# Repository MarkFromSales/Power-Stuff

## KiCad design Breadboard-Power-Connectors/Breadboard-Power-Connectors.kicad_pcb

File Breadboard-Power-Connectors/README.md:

# Breadboard Power Connectors
I got tired of dealing with mediocre screw terminals on breadboard panels and made this to use banana jacks to link to terminal blocks. There are two pairs spaced to match dual-banana connector cables. One pair has through-hole spaces that either need diodes as designed, a fuse, or simple bridge to connect it through.

## Materials so far

ID | Description | Digi-Key PN
-- | ----------- | -----------
Dx | Schottky Diode Through Hole DO-27, Axial | 80SQ045NRLGOSCT-ND
J2,J4,J6,J8 | TE Connectivity AMP Connectors 01x04 screw terminal block | A98335-ND
J1 | Cal Test Electronics Banana Jack Panel Mount, Through Hole, Right Angle	BLACK  | BKCT3151SP-0-ND
J3 | Cal Test Electronics Banana Jack Panel Mount, Through Hole, Right Angle	RED    | BKCT3151SP-2-ND
J5 | Cal Test Electronics Banana Jack Panel Mount, Through Hole, Right Angle	YELLOW | BKCT3151SP-4-ND
J7 | Cal Test Electronics Banana Jack Panel Mount, Through Hole, Right Angle	GREEN  | BKCT3151SP-5-ND

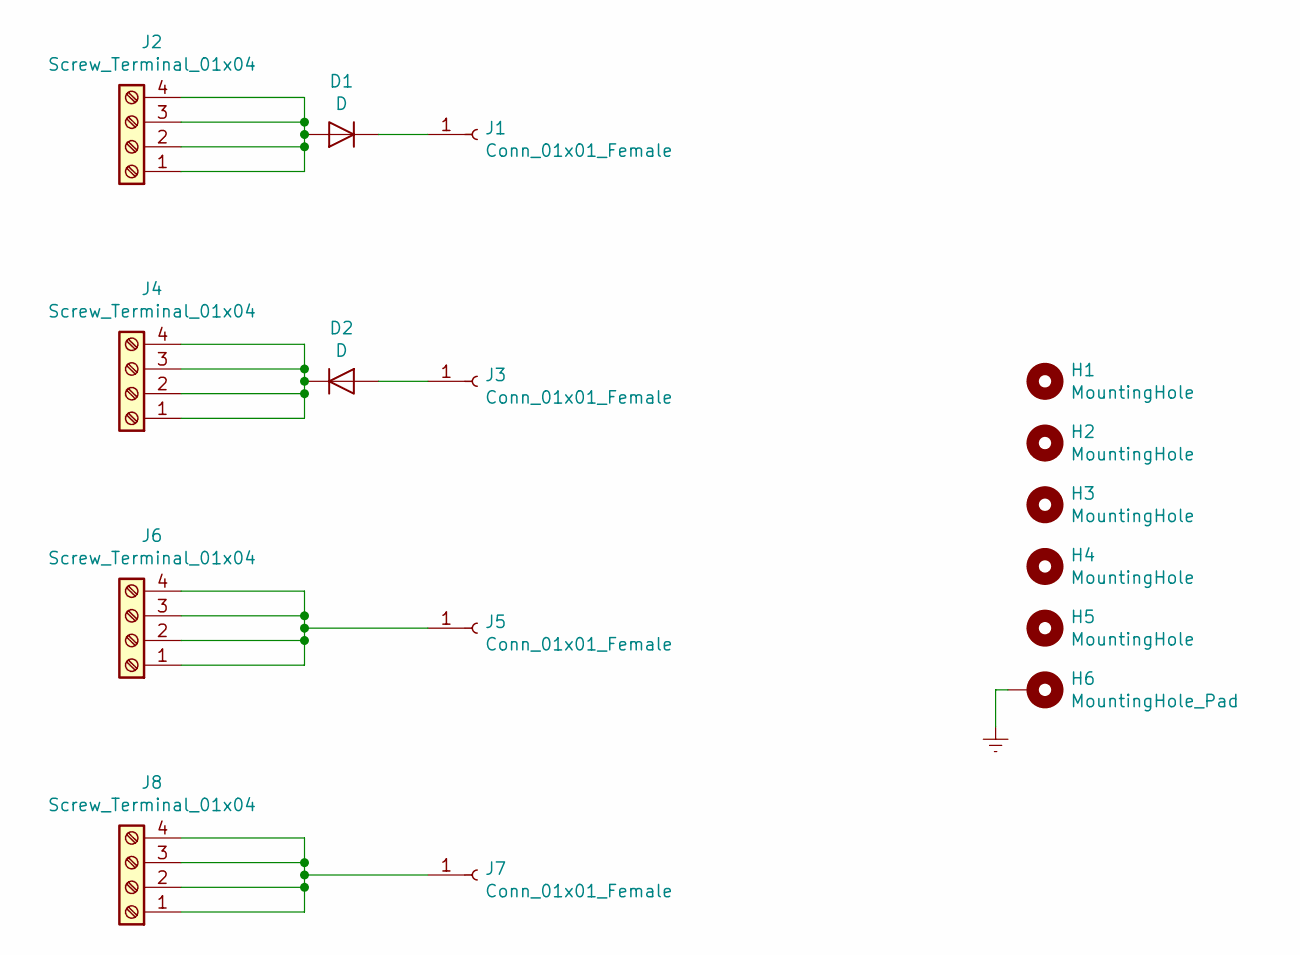
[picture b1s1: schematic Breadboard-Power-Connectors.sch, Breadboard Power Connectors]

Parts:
D1, D2: D; D_DO-27_P12.70mm_Horizontal
H1, H2, H3, H4, H5: MountingHole; MountingHole_3.2mm_M3
H6: MountingHole_Pad; MountingHole_3.2mm_M3_Pad
J1, J3, J5, J7: Conn_01x01_Female; CalTest_CT3151
J2, J4, J6, J8: Screw_Terminal_01x04; TerminalBlock_TE_282834-4_1x04_P2.54mm_Horizontal

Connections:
Earth: H6.1
unnamed: D1.1 (K), J1.1
unnamed: D1.2 (A), J2.1, J2.2, J2.3, J2.4
unnamed: D2.1 (K), J4.1, J4.2, J4.3, J4.4
unnamed: D2.2 (A), J3.1
unnamed: J5.1, J6.1, J6.2, J6.3, J6.4
unnamed: J7.1, J8.1, J8.2, J8.3, J8.4

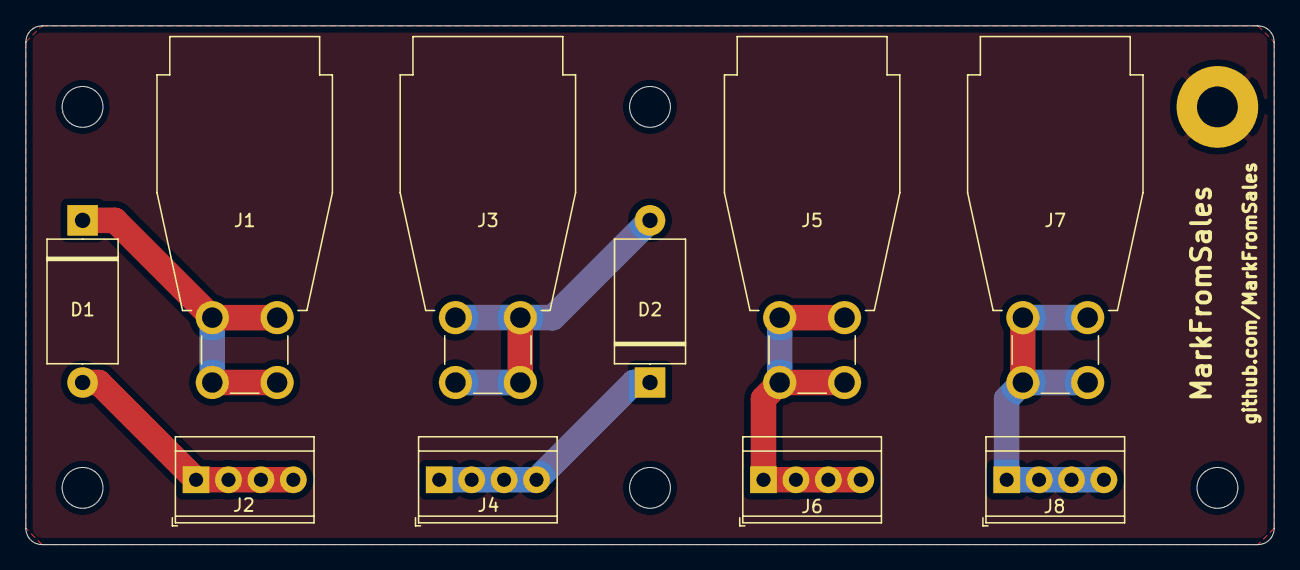
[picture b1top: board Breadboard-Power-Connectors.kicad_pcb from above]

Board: 2 copper layers, 97.8 x 40.6 mm, 16 parts (0 on the bottom side), 6 nets.

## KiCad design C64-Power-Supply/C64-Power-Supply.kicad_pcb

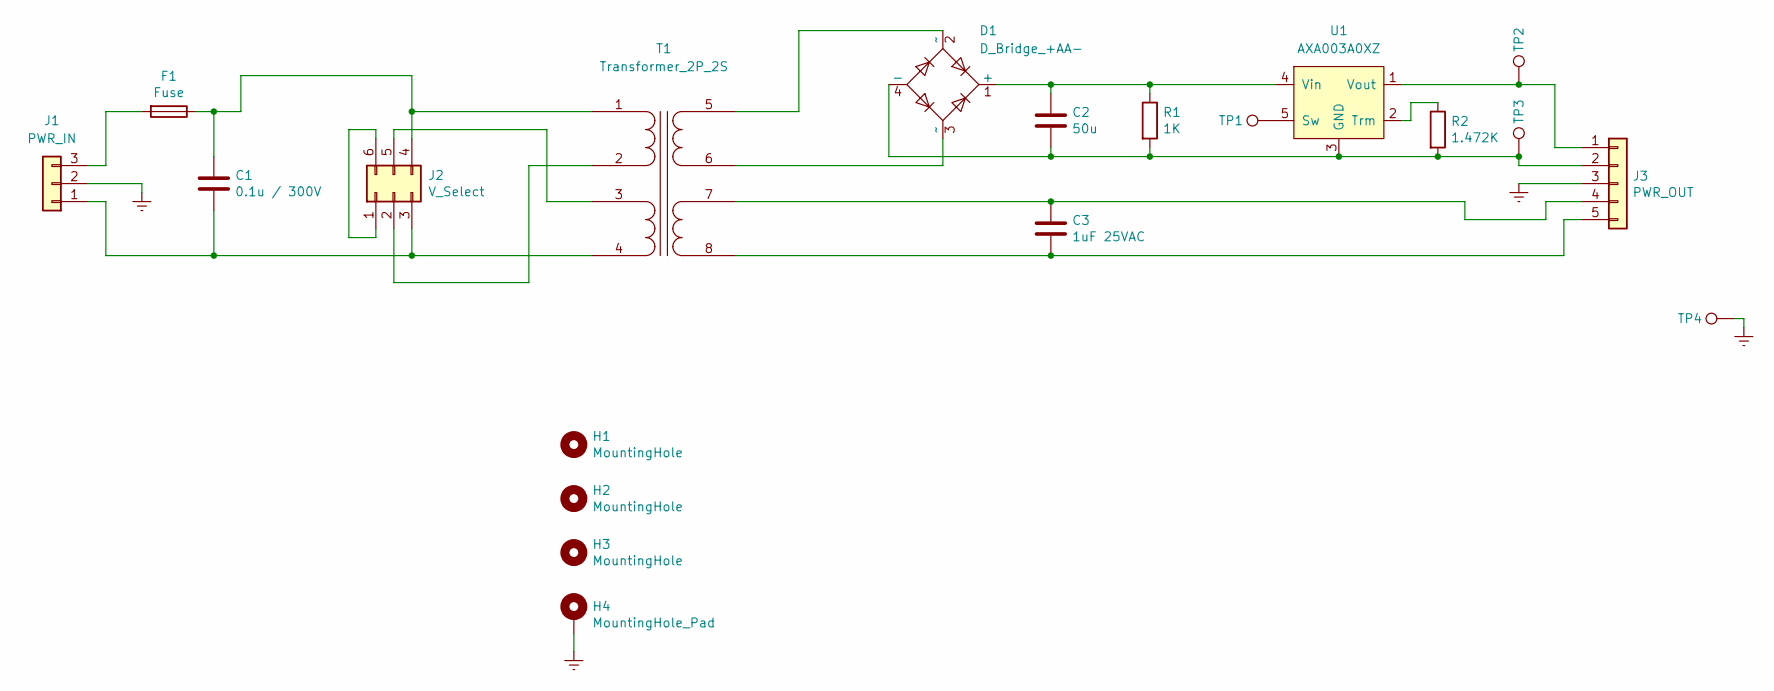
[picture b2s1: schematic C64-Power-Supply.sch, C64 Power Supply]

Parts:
C1: 0.1u / 300V; C_Rect_L26.5mm_W10.5mm_P22.50mm_MKS4
C2: 50u; CP_Axial_L25.0mm_D10.0mm_P30.00mm_Horizontal
C3: 1uF 25VAC; C_Rect_L18.0mm_W11.0mm_P15.00mm_FKS3_FKP3
D1: D_Bridge_+AA-; Diode_Bridge_Vishay_GBU
F1: Fuse; JST_VH_B2P-VH_1x02_P3.96mm_Vertical
H1, H2, H3: MountingHole; MountingHole_3.2mm_M3
H4: MountingHole_Pad; MountingHole_3.2mm_M3_Pad
J1: PWR_IN; JST_VH_B3P-VH_1x03_P3.96mm_Vertical
J2: V_Select; JST_VH_B6P-VH_1x06_P3.96mm_Vertical
J3: PWR_OUT; JST_VH_B5P-VH_1x05_P3.96mm_Vertical
R1: 1K; R_1206_3216Metric_Pad1.42x1.75mm_HandSolder
R2: 1.472K; R_1206_3216Metric_Pad1.42x1.75mm_HandSolder
T1: Transformer_2P_2S; Amgis_L01-6371
TP1, TP2, TP3, TP4: TestPoint; TestPoint_Pad_D2.5mm
U1: AXA003A0XZ

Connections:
Earth: H4.1, J1.2, J3.3, TP4.1
unnamed: C1.1, F1.1, J2.4, T1.1 (IN1A)
unnamed: C1.2, J1.1, J2.3, T1.4 (IN2B)
unnamed: C2.1, D1.1 (+), R1.1, U1.4 (Vin)
unnamed: C2.2, D1.4 (-), J3.2, R1.2, R2.2, TP3.1, U1.3 (GND)
unnamed: C3.1, J3.4, T1.7 (OUT2A)
unnamed: C3.2, J3.5, T1.8 (OUT2B)
unnamed: D1.2 (~~), T1.5 (OUT1A)
unnamed: D1.3 (~~), T1.6 (OUT1B)
unnamed: F1.2, J1.3
unnamed: J2.1, J2.6
unnamed: J2.2, T1.2 (IN1B)
unnamed: J2.5, T1.3 (IN2A)
unnamed: J3.1, TP2.1, U1.1 (Vout)
unnamed: R2.1, U1.2 (Trm)
unnamed: TP1.1, U1.5 (Sw)

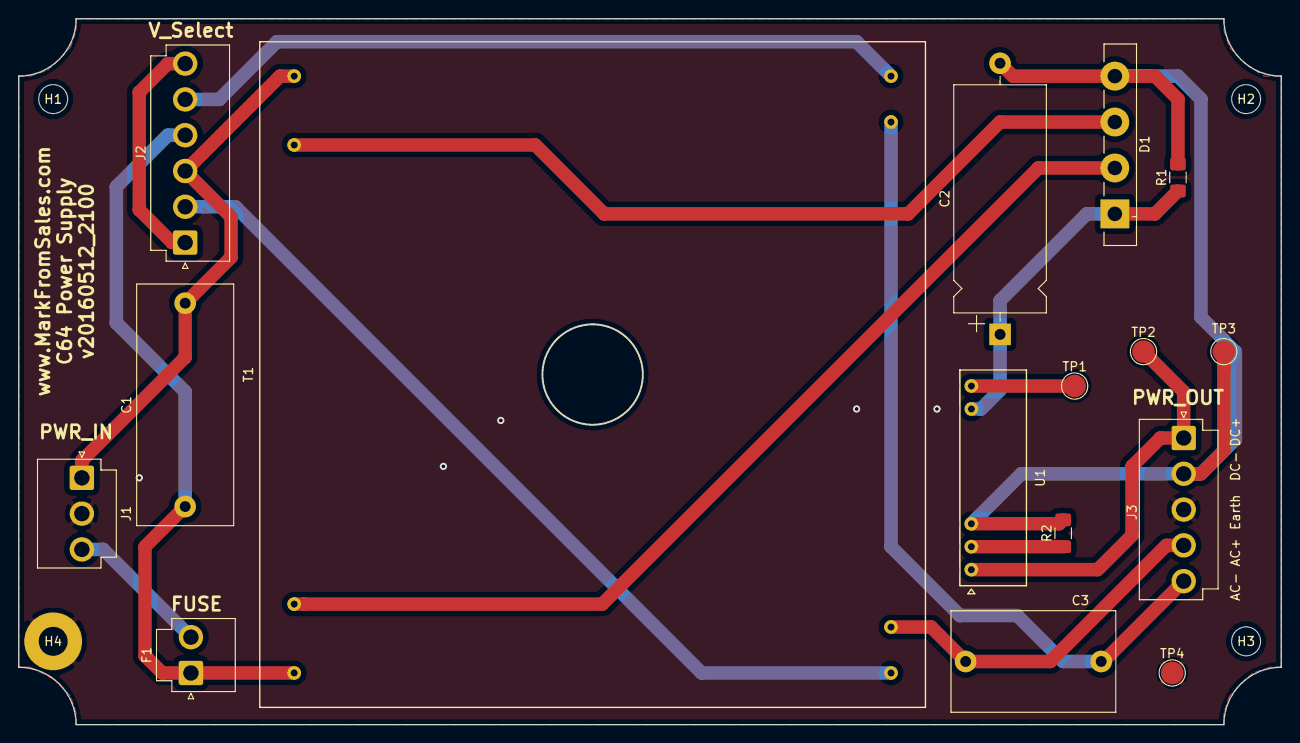
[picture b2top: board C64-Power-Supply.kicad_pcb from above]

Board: 2 copper layers, 139.7 x 78.1 mm, 20 parts (0 on the bottom side), 16 nets.

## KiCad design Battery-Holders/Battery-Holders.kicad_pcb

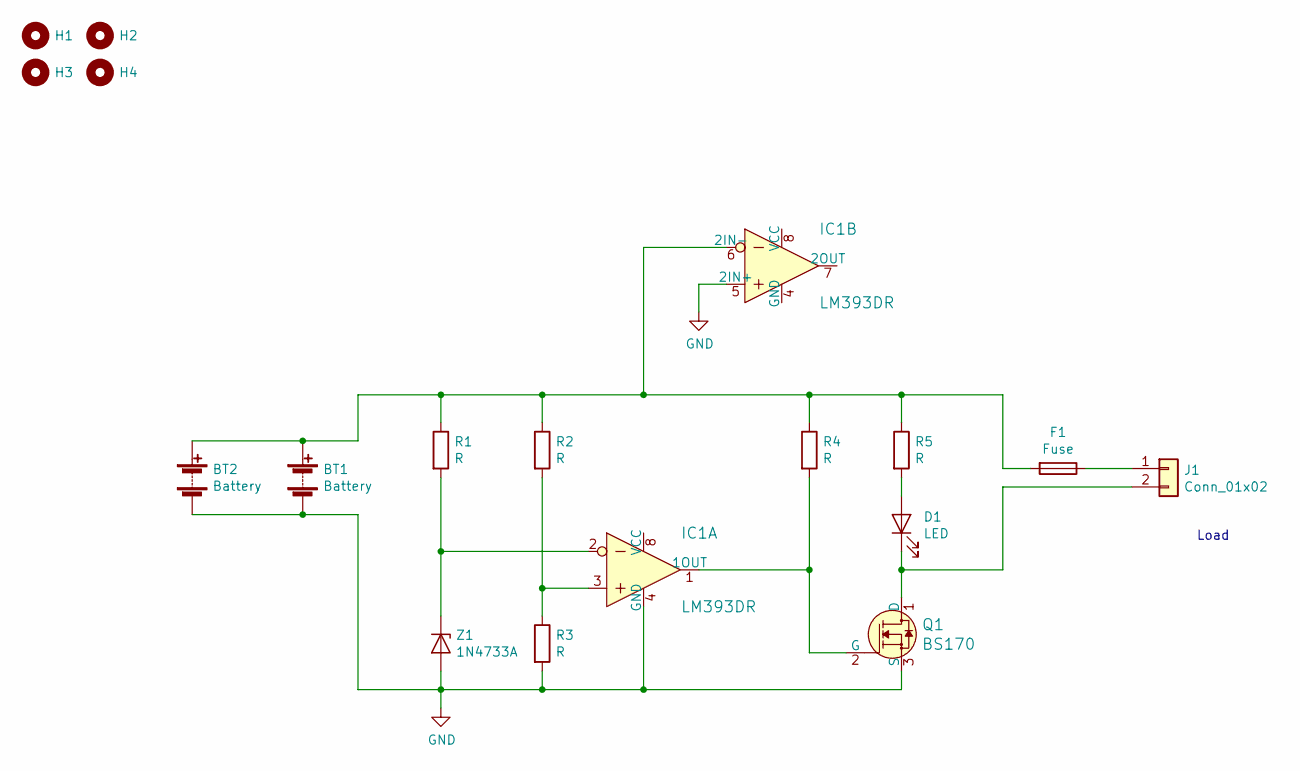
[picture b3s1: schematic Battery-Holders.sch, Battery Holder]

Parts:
BT1, BT2: Battery; BatteryHolder_MPD_BH-18650-PC2
D1: LED; LED_1206_3216Metric_Pad1.42x1.75mm_HandSolder
F1: Fuse; Fuseholder_TR5_Littelfuse_No560_No460
H1, H2, H3, H4: MountingHole; MountingHole_3.2mm_M3
IC1: LM393DR; SOIC-8_3.9x4.9mm_P1.27mm; MPN LM393DR; Digi-Key_PN 296-1015-1-ND
J1: Conn_01x02; JST_VH_B2P-VH_1x02_P3.96mm_Vertical
Q1: BS170; TO-92_Inline_Wide; MPN BS170; Digi-Key_PN BS170-ND
R1, R2, R3, R4, R5: R; R_1206_3216Metric_Pad1.42x1.75mm_HandSolder
Z1: 1N4733A; D_DO-41_SOD81_P10.16mm_Horizontal

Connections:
GND: BT1.2 (-), BT2.2 (-), IC1.4 (GND), IC1.5 (2IN+), Q1.3 (S), R3.2, Z1.2 (A)
unnamed: BT1.1 (+), BT2.1 (+), F1.2, IC1.6 (2IN-), R1.1, R2.1, R4.1, R5.1
unnamed: D1.1 (K), J1.2, Q1.1 (D)
unnamed: D1.2 (A), R5.2
unnamed: F1.1, J1.1
unnamed: IC1.1 (1OUT), Q1.2 (G), R4.2
unnamed: IC1.2, R1.2, Z1.1 (K)
unnamed: IC1.3, R2.2, R3.1

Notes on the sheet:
Load

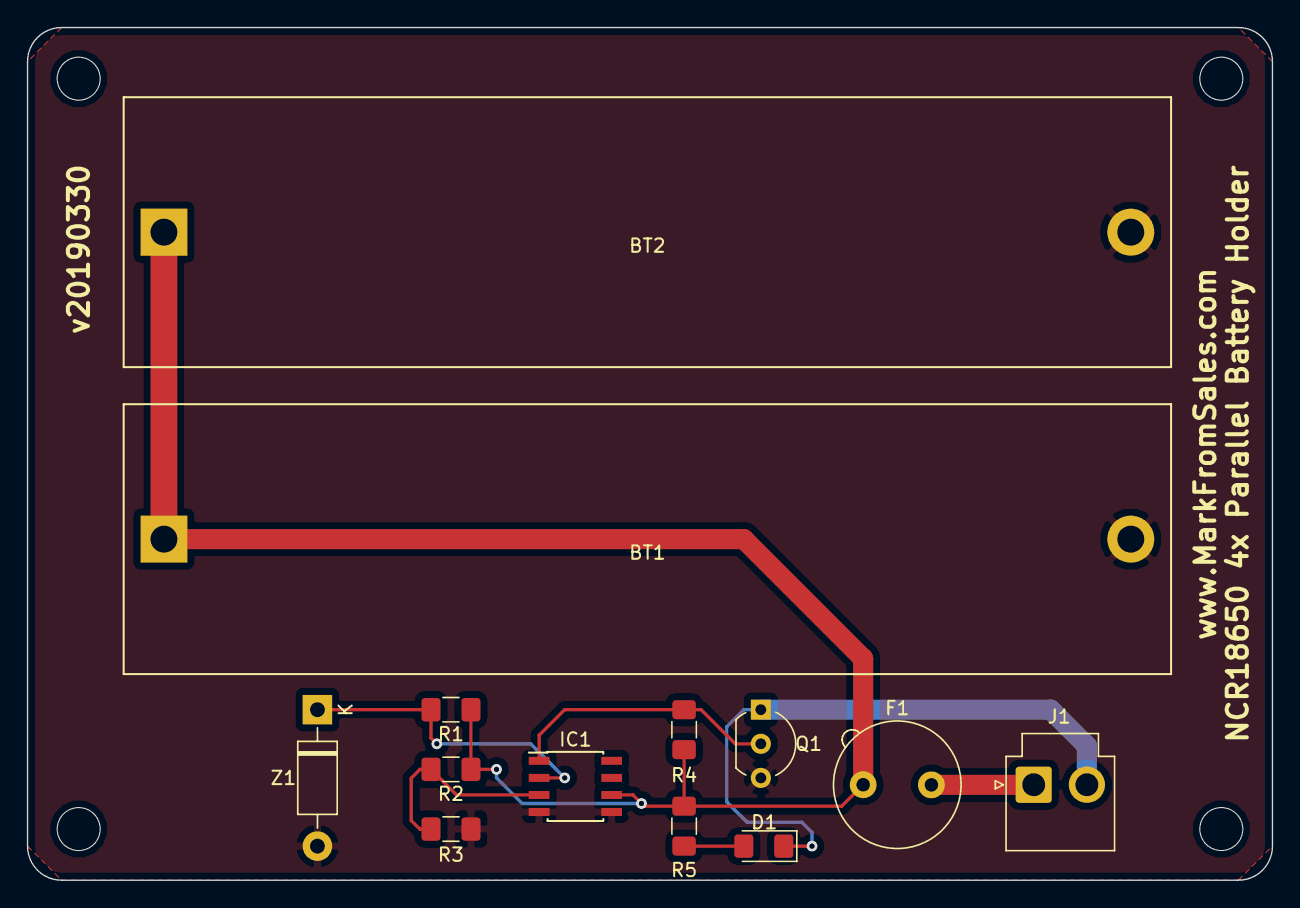
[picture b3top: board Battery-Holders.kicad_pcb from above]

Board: 2 copper layers, 92.7 x 63.5 mm, 17 parts (0 on the bottom side), 8 nets.

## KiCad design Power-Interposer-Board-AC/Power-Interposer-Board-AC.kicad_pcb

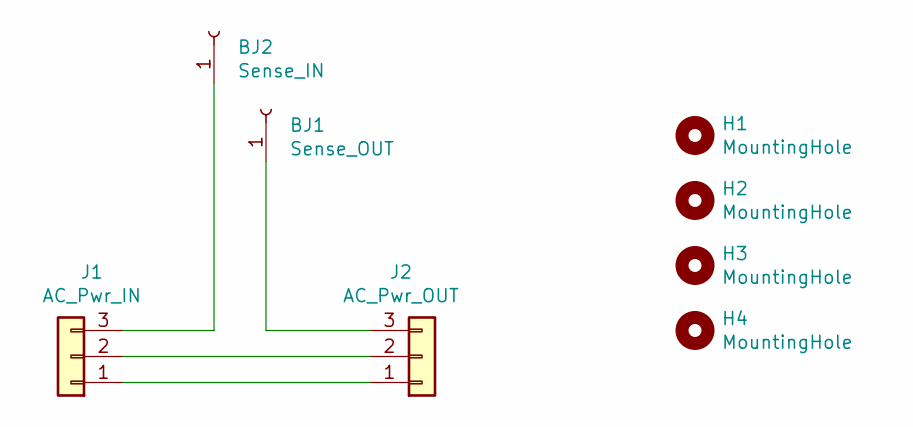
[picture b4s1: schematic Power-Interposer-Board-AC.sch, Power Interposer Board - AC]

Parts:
BJ1: Sense_OUT; CalTest_CT3151
BJ2: Sense_IN; CalTest_CT3151
H1, H2, H3, H4: MountingHole; MountingHole_3.2mm_M3
J1: AC_Pwr_IN; JST_VH_B3PS-VH_1x03_P3.96mm_Horizontal
J2: AC_Pwr_OUT; JST_VH_B3PS-VH_1x03_P3.96mm_Horizontal

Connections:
unnamed: BJ1.1, J2.3
unnamed: BJ2.1, J1.3
unnamed: J1.1, J2.1
unnamed: J1.2, J2.2

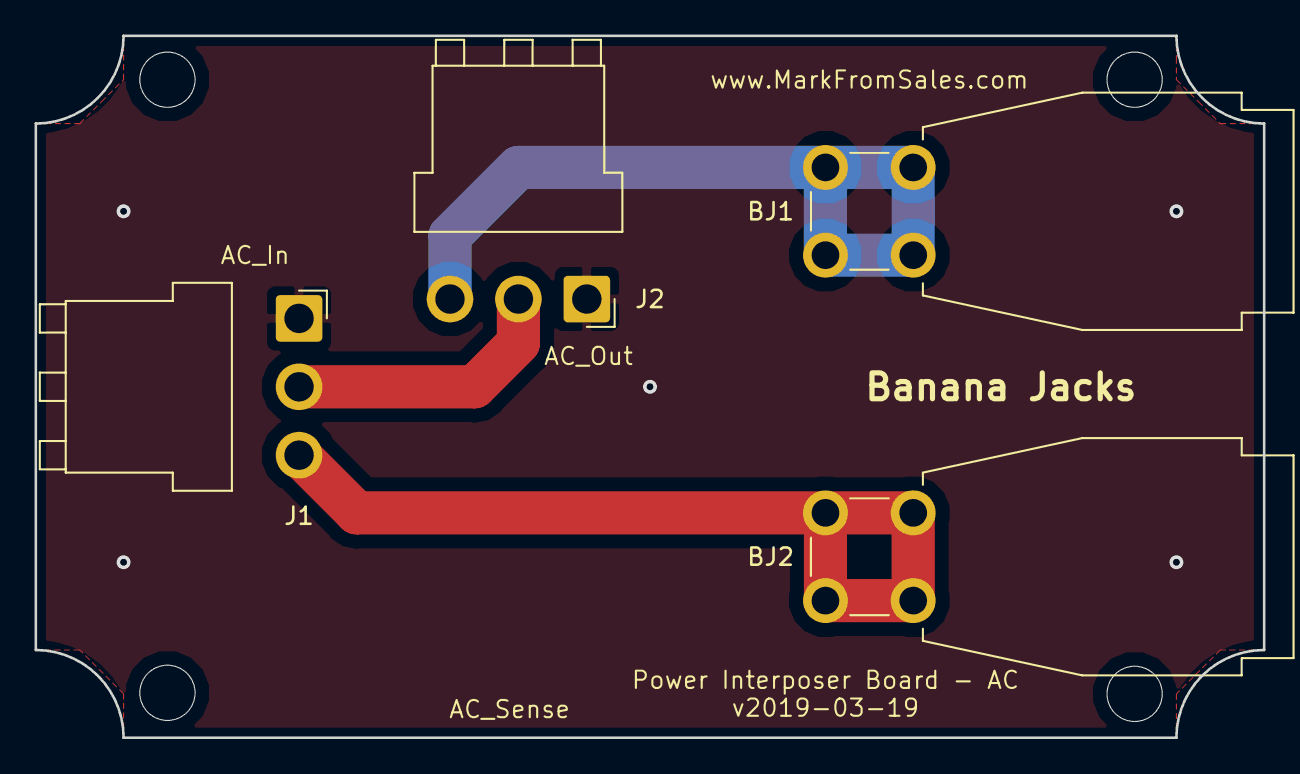
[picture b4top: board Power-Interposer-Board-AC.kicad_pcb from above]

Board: 2 copper layers, 71.1 x 40.6 mm, 8 parts (0 on the bottom side), 4 nets.

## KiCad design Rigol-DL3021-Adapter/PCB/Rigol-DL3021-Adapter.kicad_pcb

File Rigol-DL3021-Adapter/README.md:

# Rigol-DL3021-Adapter
Banana jack adapter for the Rigol DL3021 DC Electronic Load

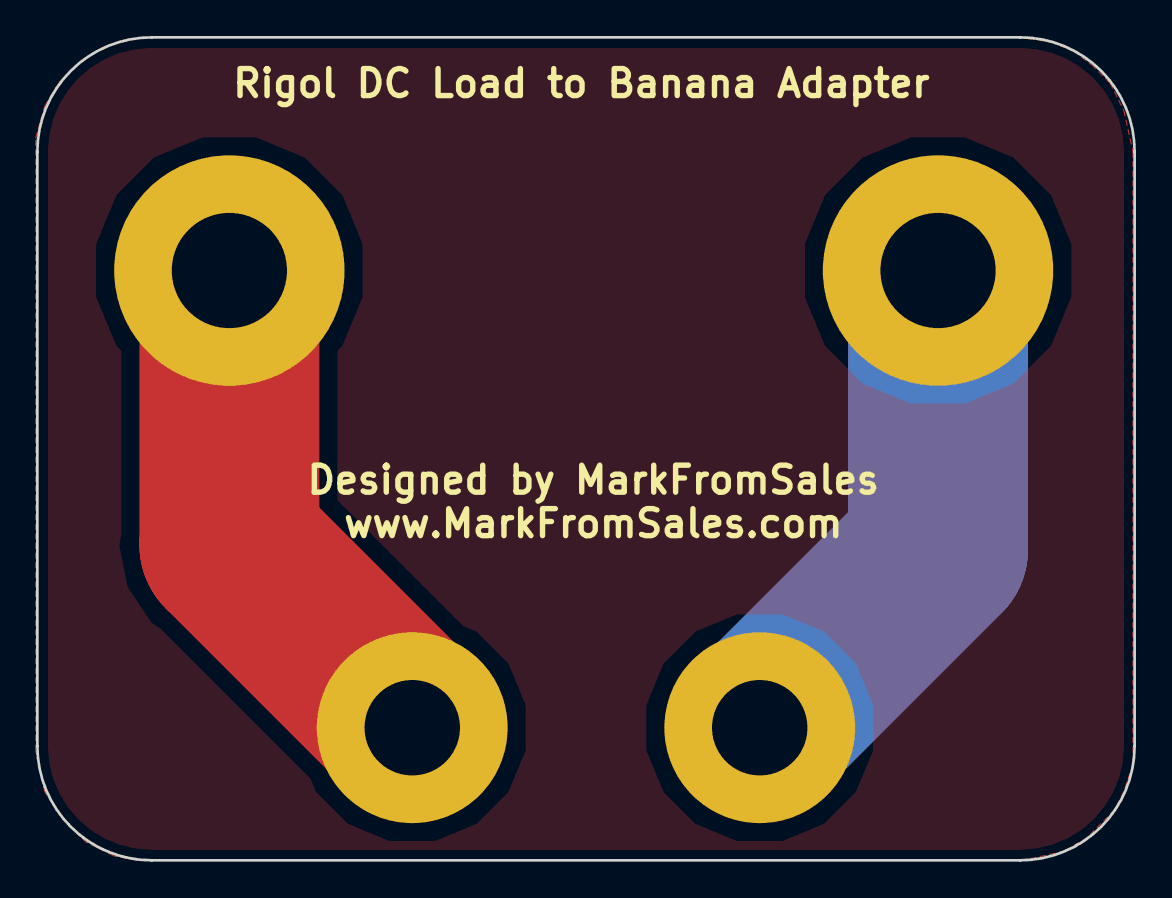
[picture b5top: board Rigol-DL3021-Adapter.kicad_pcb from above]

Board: 2 copper layers, 61.0 x 45.7 mm, 4 parts (0 on the bottom side), 2 nets.

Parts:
H1, H2: MountingHole_Pad; MountingHole_6.4mm_M6_Pad
H3, H4: MountingHole_Pad; MountingHole_5.3mm_M5_Pad

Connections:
unnamed: H1.1, H3.1
unnamed: H2.1, H4.1

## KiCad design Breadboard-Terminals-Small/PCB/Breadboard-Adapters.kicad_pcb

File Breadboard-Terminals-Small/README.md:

# Breadboard-Power-Terminals-Small
An adapter for brining power into multiple breadboards using screw terminals (small version)

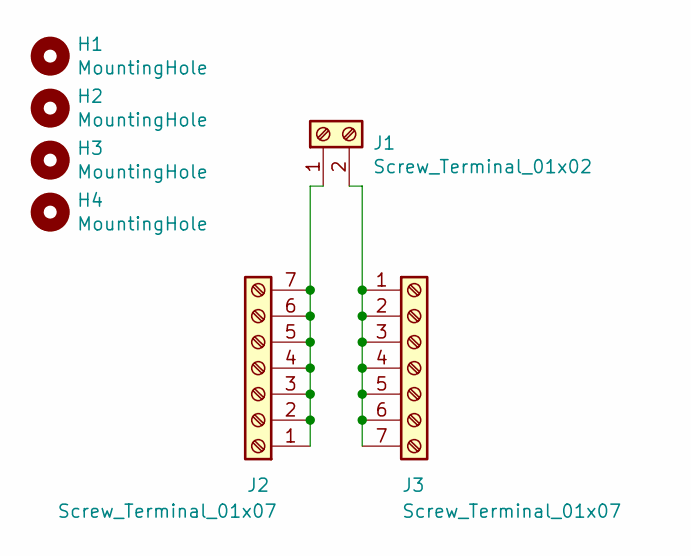
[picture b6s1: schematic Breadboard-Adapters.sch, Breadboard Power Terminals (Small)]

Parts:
H1, H2, H3, H4: MountingHole; MountingHole_3.2mm_M3
J1: Screw_Terminal_01x02; TerminalBlock_bornier-2_P5.08mm
J2, J3: Screw_Terminal_01x07; TerminalBlock_TE_282834-7_1x07_P2.54mm_Horizontal

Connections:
unnamed: J1.1, J2.1, J2.2, J2.3, J2.4, J2.5, J2.6, J2.7
unnamed: J1.2, J3.1, J3.2, J3.3, J3.4, J3.5, J3.6, J3.7

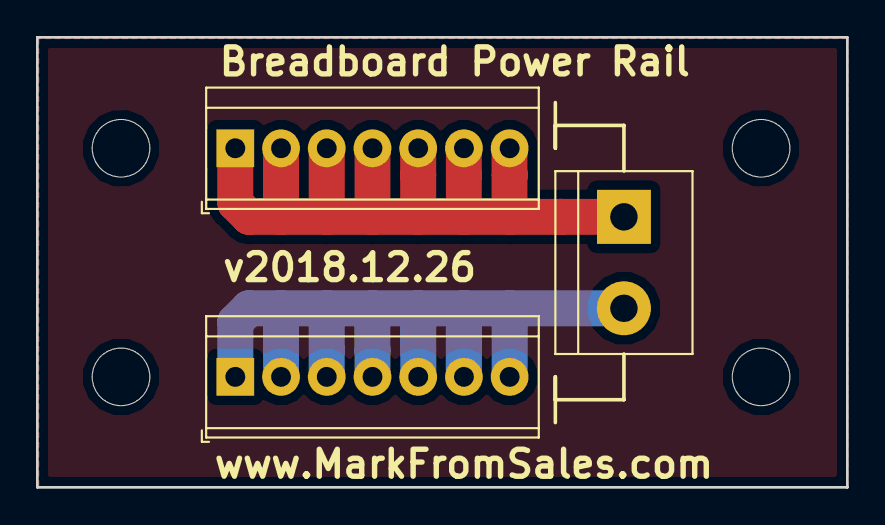
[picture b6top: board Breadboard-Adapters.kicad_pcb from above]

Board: 2 copper layers, 45.0 x 25.0 mm, 7 parts (0 on the bottom side), 2 nets.

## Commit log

2019-02-10 Initial Upload
2019-02-13 Updated structure
2019-03-19 New board for AC measurements with DMM
2019-03-25 Minor Updates
2019-04-01 minor
2019-05-12 C64 Power Supply Initial
2019-05-12 Added exports
2019-05-13 Added 5VDC regulation
2020-04-18 Initial
    First shot
2020-04-18 Screenshots
    Added screenshots of the schematic and pcb
